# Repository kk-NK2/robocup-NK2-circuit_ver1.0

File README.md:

交流会用に作った初めての回路です。
らずピコとアルディーノのuart通信でレベル変換をしていなかったため、燃えます。

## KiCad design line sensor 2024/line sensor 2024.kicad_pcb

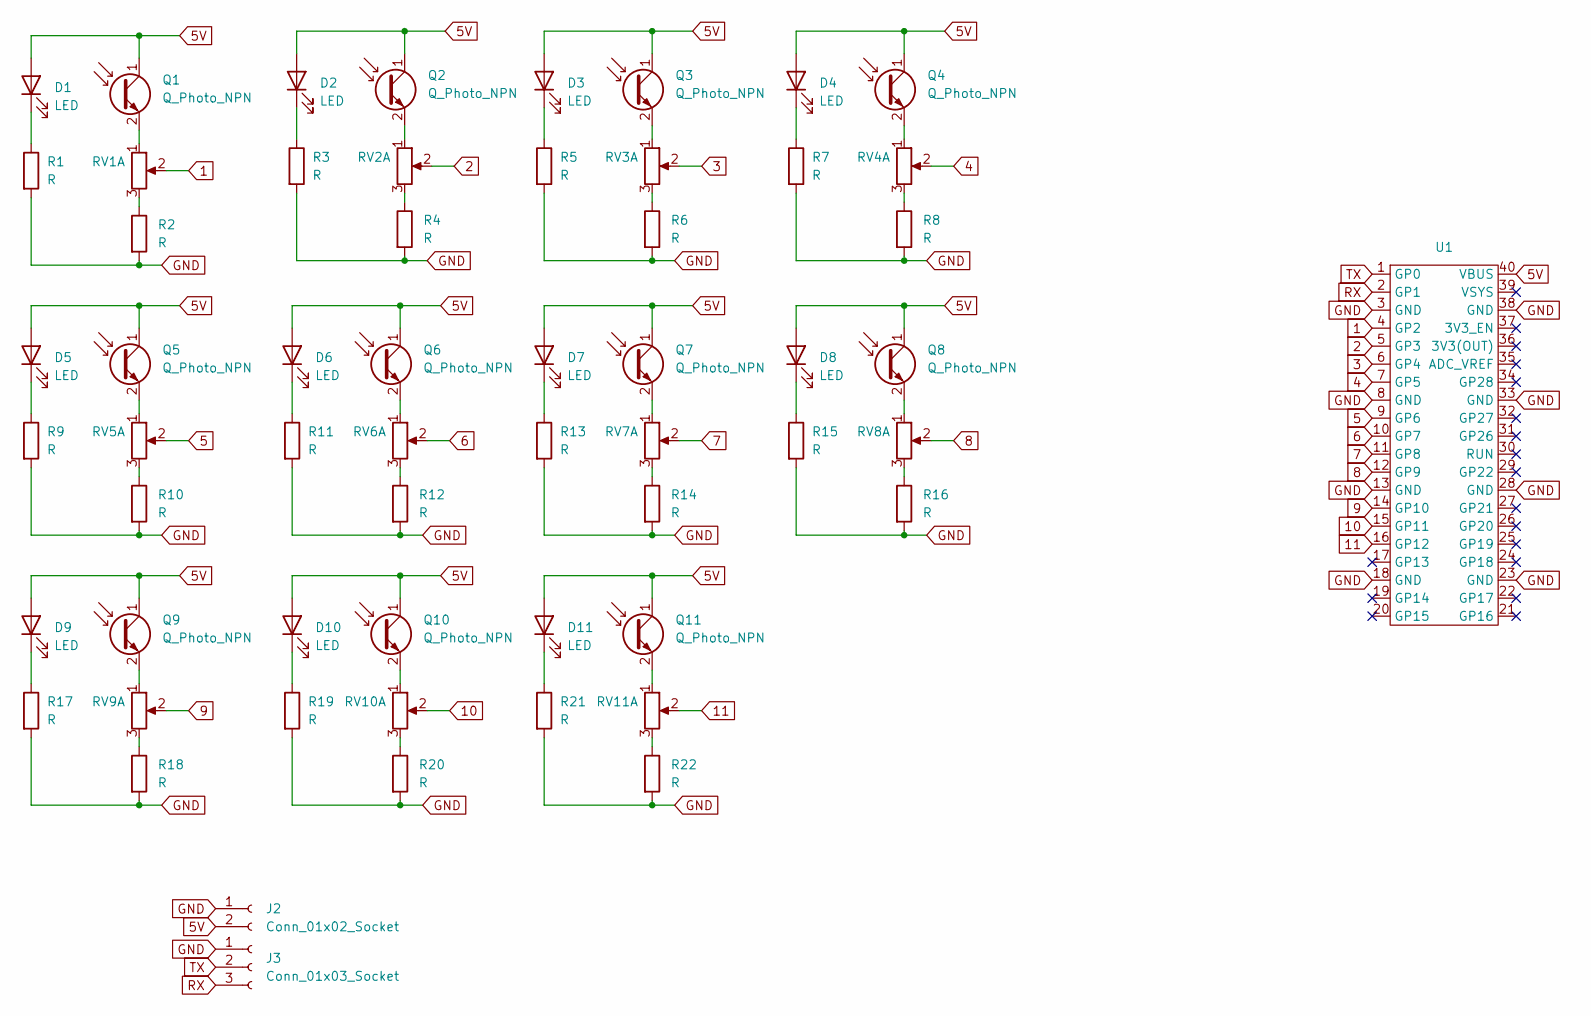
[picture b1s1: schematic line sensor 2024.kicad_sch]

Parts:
D1, D2, D3, D4, D5, D6, D7, D8, D9, D10, D11: LED; LED_D3.0mm_Clear
J2: Conn_01x02_Socket; JST_XH_B2B-XH-AM_1x02_P2.50mm_Vertical
J3: Conn_01x03_Socket; JST_XH_B3B-XH-AM_1x03_P2.50mm_Vertical
Q1, Q2, Q3, Q4, Q5, Q6, Q7, Q8, Q9, Q10, Q11: Q_Photo_NPN; LED_D4.0mm
R1, R2, R3, R4, R5, R6, R7, R8, R9, R10, R11, R12, R13, R14, R15, R16, R17, R18, R19, R20, R21, R22: R; R_Axial_DIN0207_L6.3mm_D2.5mm_P10.16mm_Horizontal
RV1, RV2, RV3, RV4, RV5, RV6, RV7, RV8, RV9, RV10, RV11: R_Potentiometer_Dual_Separate; Potentiometer_Vishay_T73YP_Vertical
U1: RP pico

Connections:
1: RV1.2, U1.4 (GP2)
2: RV2.2, U1.5 (GP3)
3: RV3.2, U1.6 (GP4)
4: RV4.2, U1.7 (GP5)
5: RV5.2, U1.9 (GP6)
5V: D1.2 (A), D2.2 (A), D3.2 (A), D4.2 (A), D5.2 (A), D6.2 (A), D7.2 (A), D8.2 (A), D9.2 (A), D10.2 (A), D11.2 (A), J2.2, Q1.1 (C), Q2.1 (C), Q3.1 (C), Q4.1 (C), Q5.1 (C), Q6.1 (C), Q7.1 (C), Q8.1 (C), Q9.1 (C), Q10.1 (C), Q11.1 (C), U1.40 (VBUS)
6: RV6.2, U1.10 (GP7)
7: RV7.2, U1.11 (GP8)
8: RV8.2, U1.12 (GP9)
9: RV9.2, U1.14 (GP10)
10: RV10.2, U1.15 (GP11)
11: RV11.2, U1.16 (GP12)
GND: J2.1, J3.1, R1.2, R2.2, R3.2, R4.2, R5.2, R6.2, R7.2, R8.2, R9.2, R10.2, R11.2, R12.2, R13.2, R14.2, R15.2, R16.2, R17.2, R18.2, R19.2, R20.2, R21.2, R22.2, U1.3 (GND), U1.8 (GND), U1.13 (GND), U1.18 (GND), U1.23 (GND), U1.28 (GND), U1.33 (GND), U1.38 (GND)
unnamed: D1.1 (K), R1.1
unnamed: D2.1 (K), R3.1
unnamed: D3.1 (K), R5.1
unnamed: D4.1 (K), R7.1
unnamed: D5.1 (K), R9.1
unnamed: D6.1 (K), R11.1
unnamed: D7.1 (K), R13.1
unnamed: D8.1 (K), R15.1
unnamed: D9.1 (K), R17.1
unnamed: D10.1 (K), R19.1
unnamed: D11.1 (K), R21.1
unnamed: Q1.2 (E), RV1.1
unnamed: Q2.2 (E), RV2.1
unnamed: Q3.2 (E), RV3.1
unnamed: Q4.2 (E), RV4.1
unnamed: Q5.2 (E), RV5.1
unnamed: Q6.2 (E), RV6.1
unnamed: Q7.2 (E), RV7.1
unnamed: Q8.2 (E), RV8.1
unnamed: Q9.2 (E), RV9.1
unnamed: Q10.2 (E), RV10.1
unnamed: Q11.2 (E), RV11.1
unnamed: R2.1, RV1.3
unnamed: R4.1, RV2.3
unnamed: R6.1, RV3.3
unnamed: R8.1, RV4.3
unnamed: R10.1, RV5.3
unnamed: R12.1, RV6.3
unnamed: R14.1, RV7.3
unnamed: R16.1, RV8.3
unnamed: R18.1, RV9.3
unnamed: R20.1, RV10.3
unnamed: R22.1, RV11.3
RX: J3.3, U1.2 (GP1)
TX: J3.2, U1.1 (GP0)

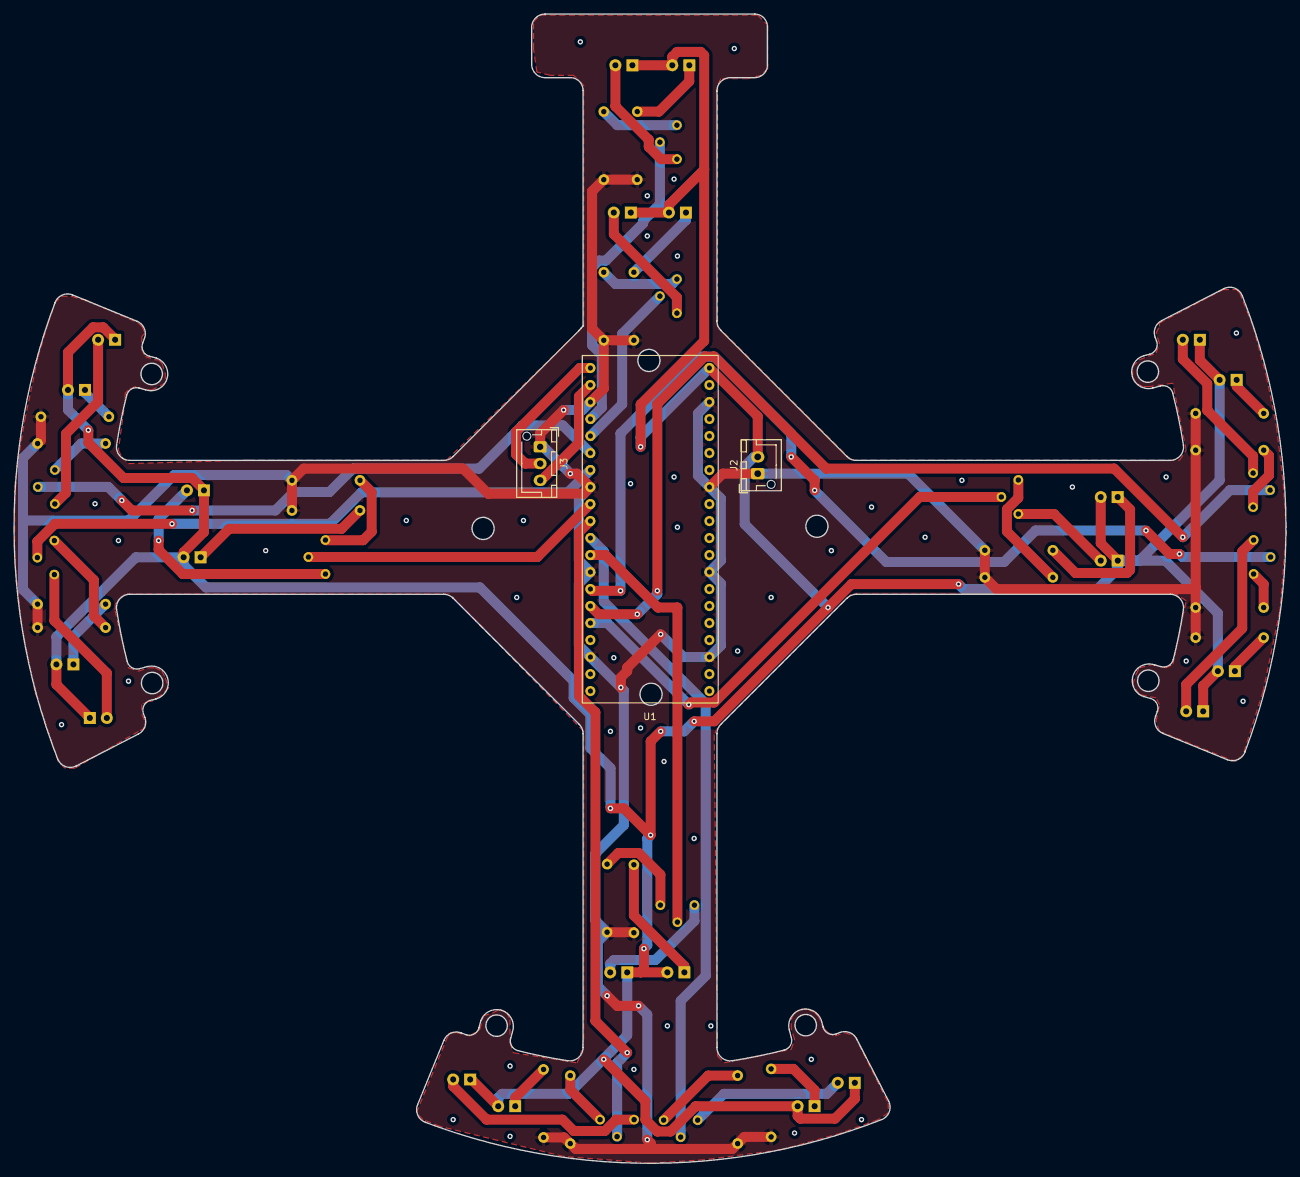
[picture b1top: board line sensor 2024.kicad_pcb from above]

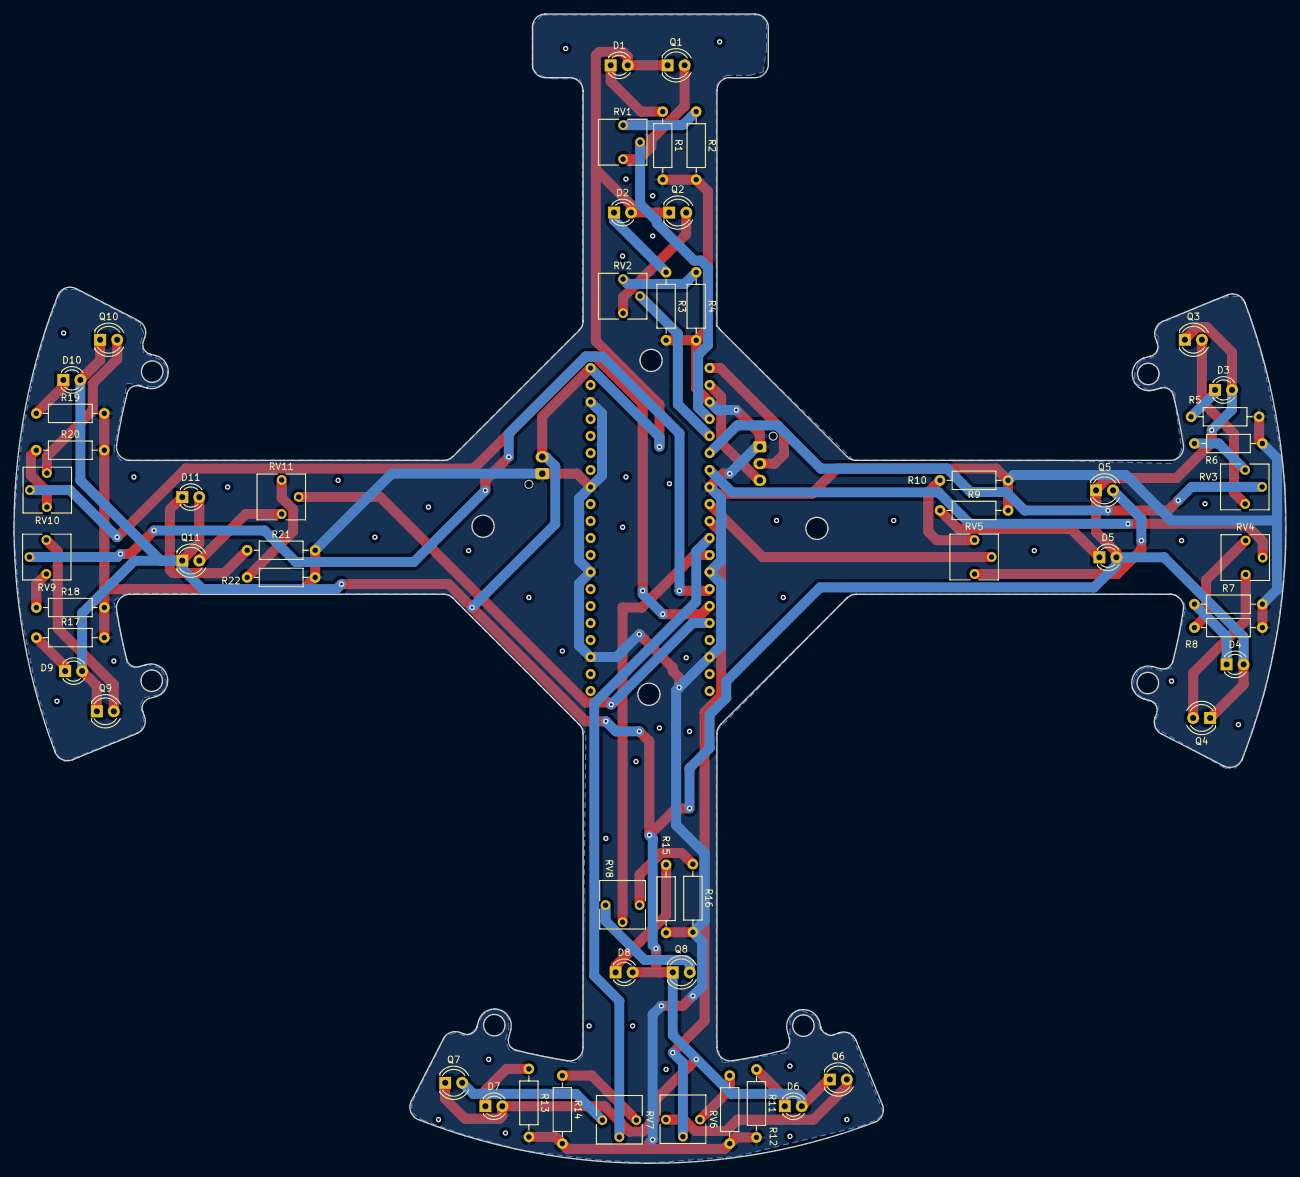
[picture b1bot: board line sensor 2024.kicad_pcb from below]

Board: 2 copper layers, 190.0 x 171.7 mm, 58 parts (55 on the bottom side), 48 nets.

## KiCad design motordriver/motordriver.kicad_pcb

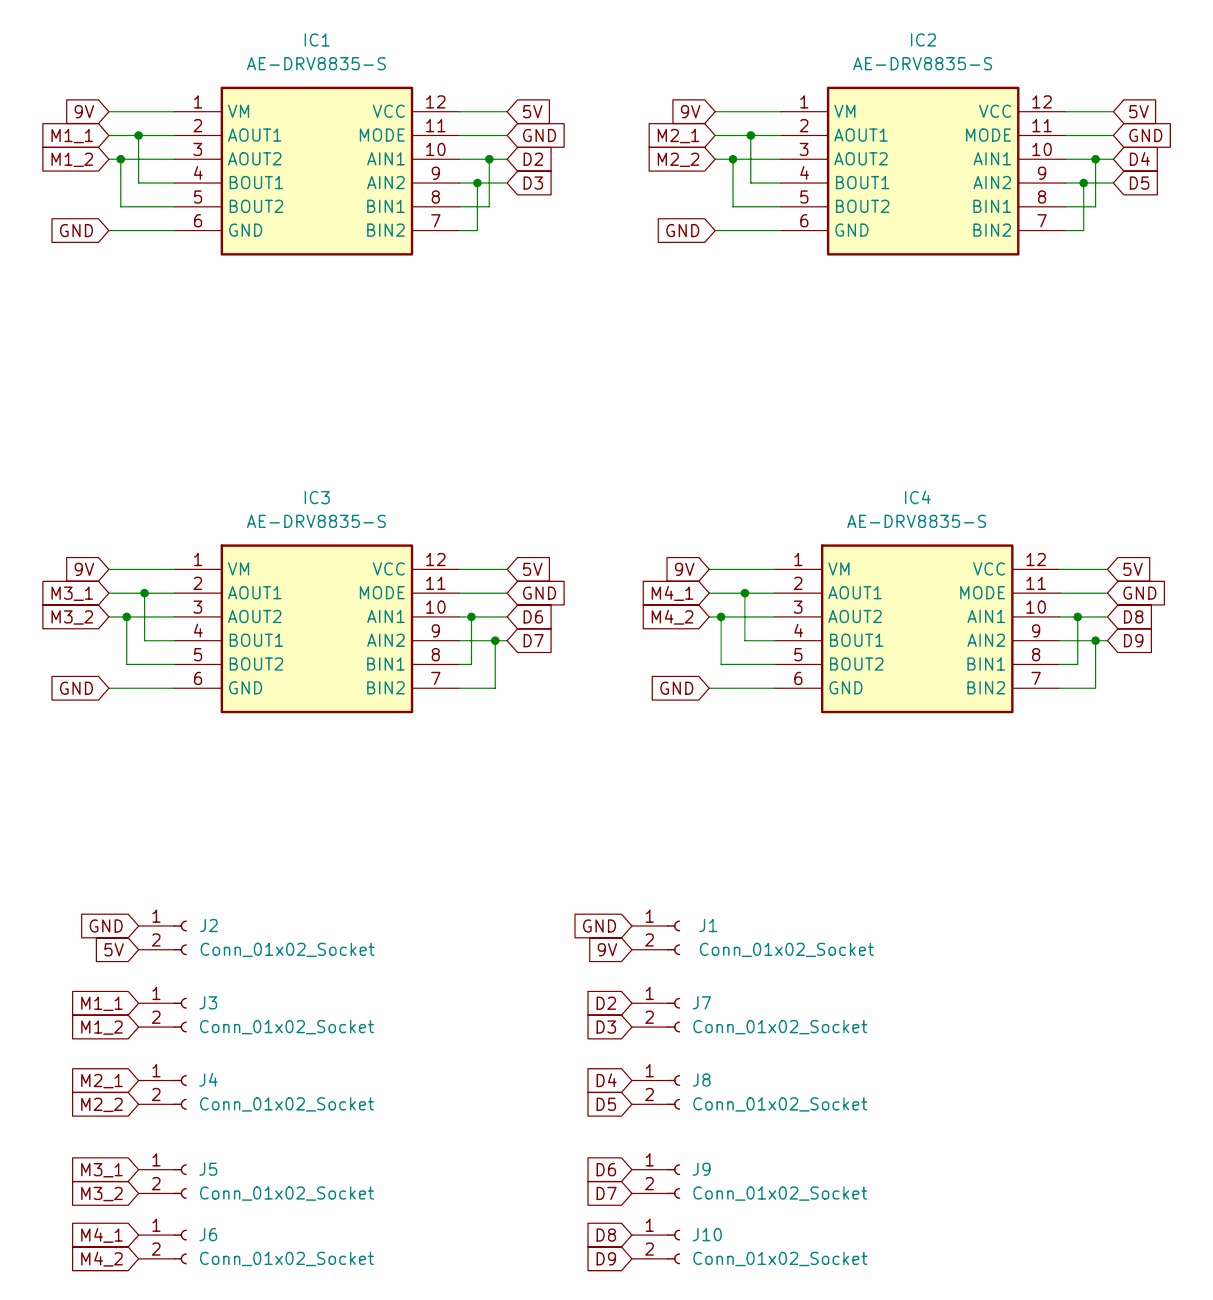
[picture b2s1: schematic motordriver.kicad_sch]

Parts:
IC1, IC2, IC3, IC4: AE-DRV8835-S; AEDRV8835S; Manufacturer_Part_Number AE-DRV8835-S
J1, J2, J3, J4, J5, J6, J7, J8, J9, J10: Conn_01x02_Socket; JST_XH_B2B-XH-AM_1x02_P2.50mm_Vertical

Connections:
5V: IC1.12 (VCC), IC2.12 (VCC), IC3.12 (VCC), IC4.12 (VCC), J2.2
9V: IC1.1 (VM), IC2.1 (VM), IC3.1 (VM), IC4.1 (VM), J1.2
D2: IC1.8 (BIN1), IC1.10 (AIN1), J7.1
D3: IC1.7 (BIN2), IC1.9 (AIN2), J7.2
D4: IC2.8 (BIN1), IC2.10 (AIN1), J8.1
D5: IC2.7 (BIN2), IC2.9 (AIN2), J8.2
D6: IC3.8 (BIN1), IC3.10 (AIN1), J9.1
D7: IC3.7 (BIN2), IC3.9 (AIN2), J9.2
D8: IC4.8 (BIN1), IC4.10 (AIN1), J10.1
D9: IC4.7 (BIN2), IC4.9 (AIN2), J10.2
GND: IC1.6 (GND), IC1.11 (MODE), IC2.6 (GND), IC2.11 (MODE), IC3.6 (GND), IC3.11 (MODE), IC4.6 (GND), IC4.11 (MODE), J1.1, J2.1
M1_1: IC1.2 (AOUT1), IC1.4 (BOUT1), J3.1
M1_2: IC1.3 (AOUT2), IC1.5 (BOUT2), J3.2
M2_1: IC2.2 (AOUT1), IC2.4 (BOUT1), J4.1
M2_2: IC2.3 (AOUT2), IC2.5 (BOUT2), J4.2
M3_1: IC3.2 (AOUT1), IC3.4 (BOUT1), J5.1
M3_2: IC3.3 (AOUT2), IC3.5 (BOUT2), J5.2
M4_1: IC4.2 (AOUT1), IC4.4 (BOUT1), J6.1
M4_2: IC4.3 (AOUT2), IC4.5 (BOUT2), J6.2

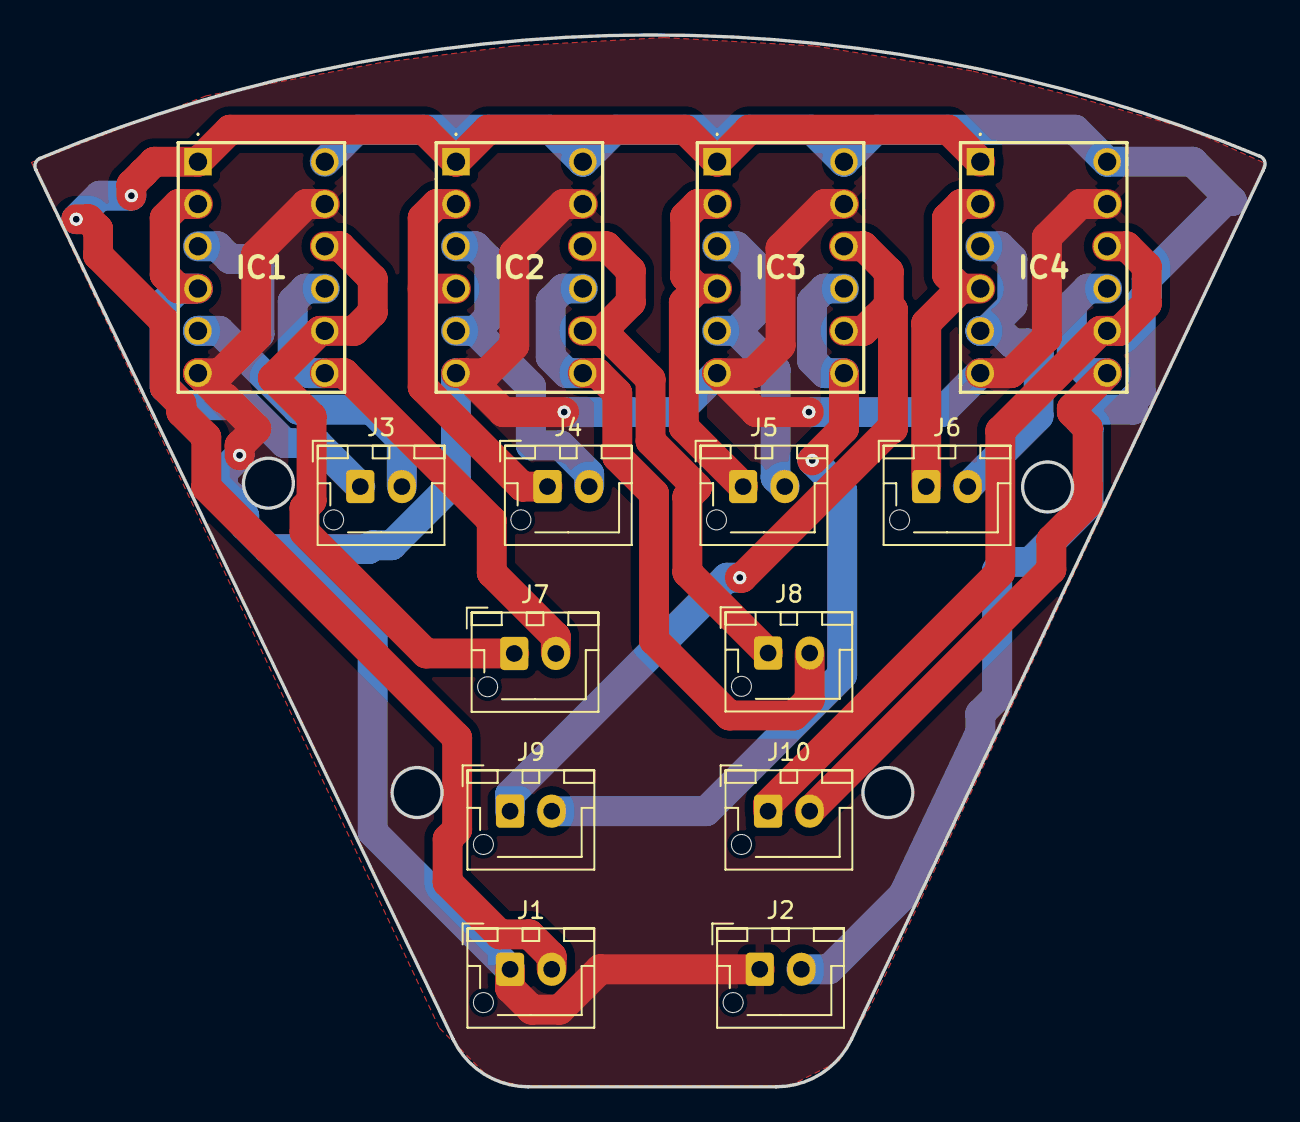
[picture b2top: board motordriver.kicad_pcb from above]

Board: 2 copper layers, 73.9 x 63.2 mm, 14 parts (0 on the bottom side), 19 nets.

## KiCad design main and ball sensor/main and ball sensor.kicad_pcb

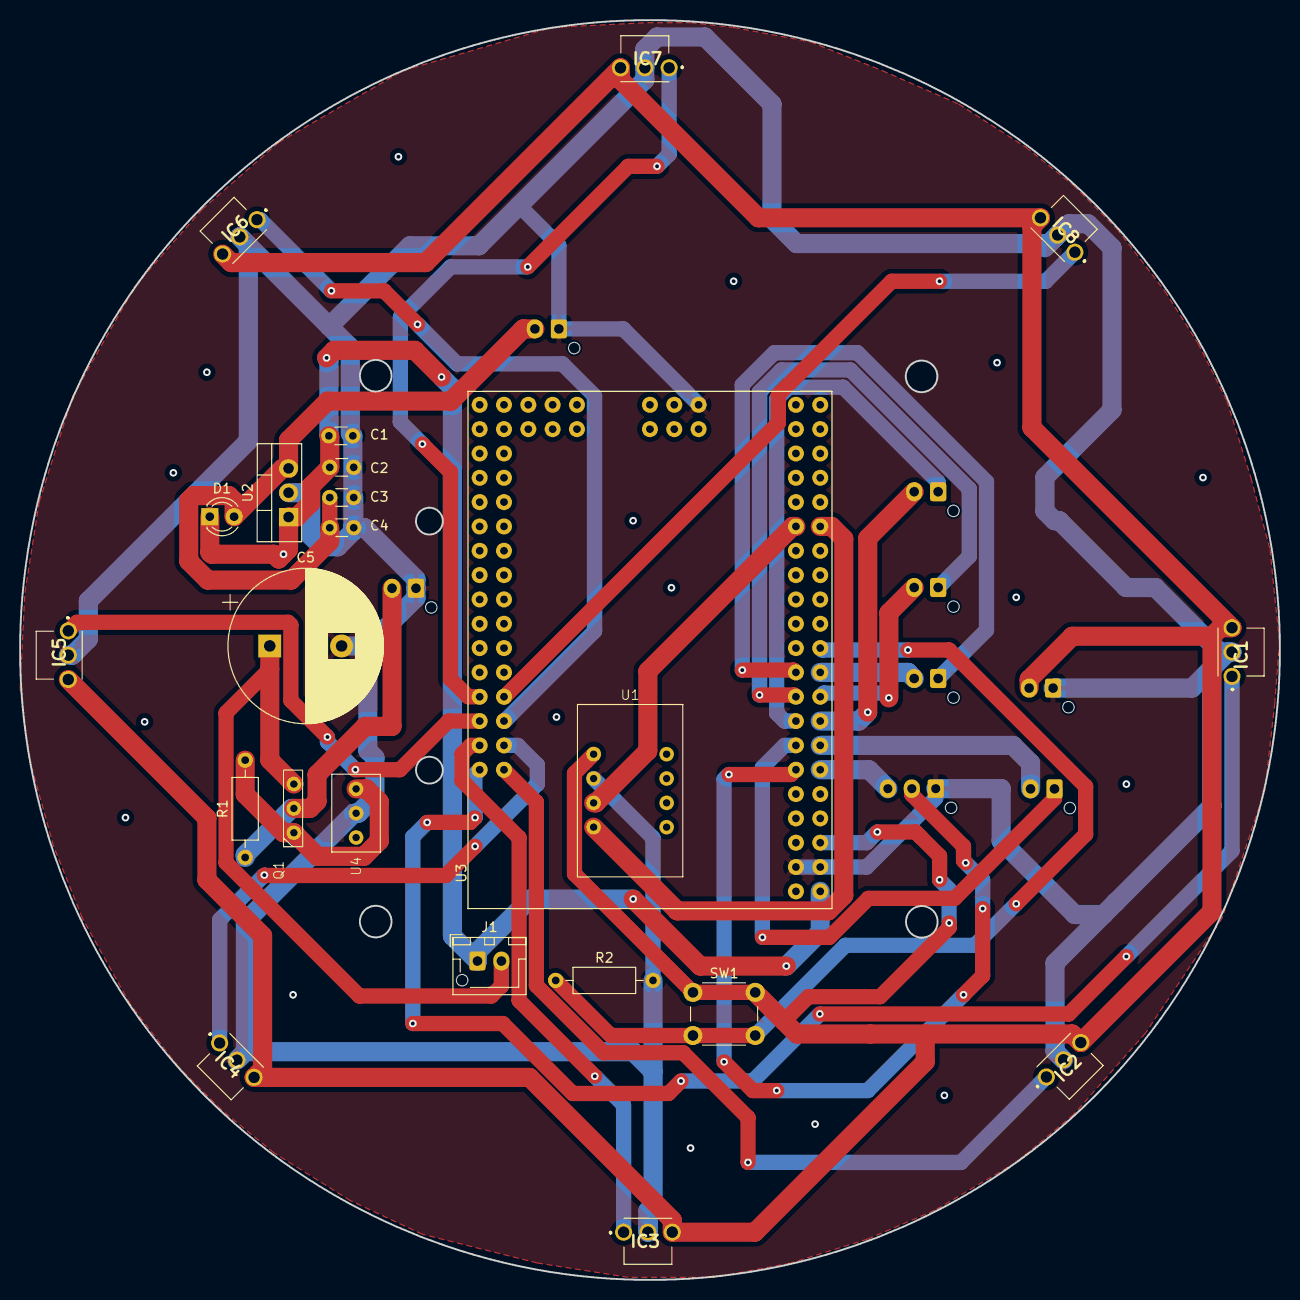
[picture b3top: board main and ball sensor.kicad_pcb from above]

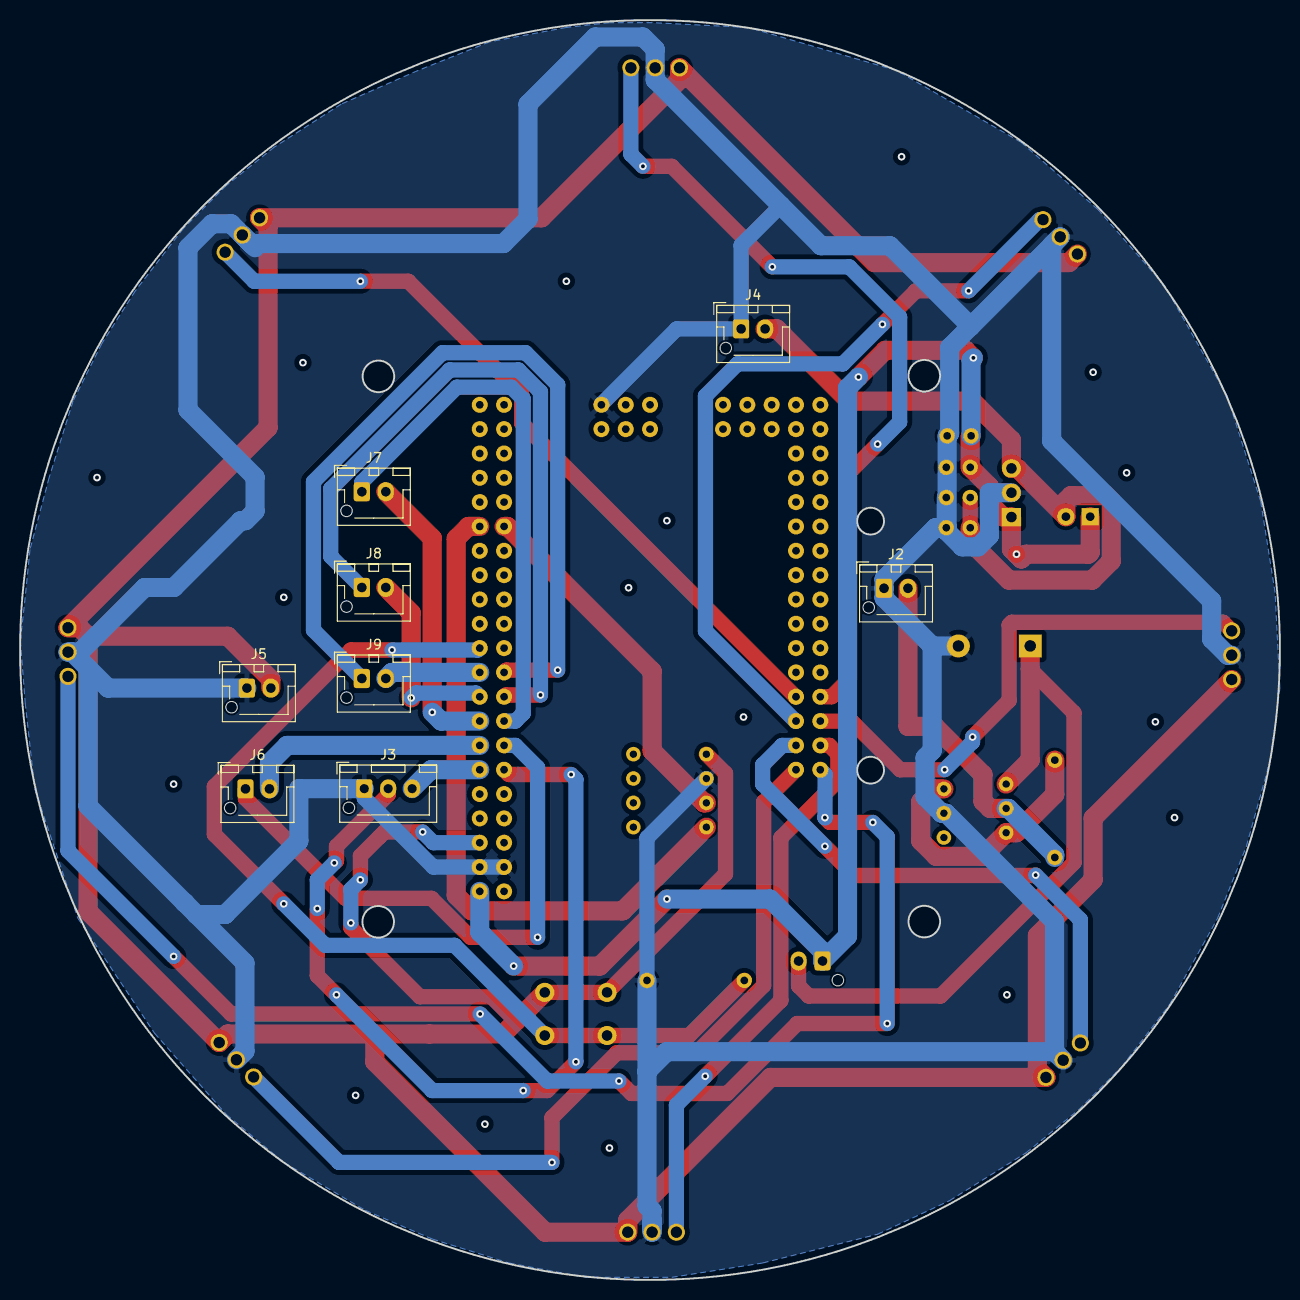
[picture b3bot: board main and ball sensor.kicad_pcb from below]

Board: 2 copper layers, 131.5 x 131.5 mm, 31 parts (8 on the bottom side), 28 nets.

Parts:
C1, C4: 0.1u; C_Disc_D3.0mm_W1.6mm_P2.50mm
C2: 10u; C_Disc_D3.0mm_W1.6mm_P2.50mm
C3: 47u; C_Disc_D3.0mm_W1.6mm_P2.50mm
C5: C_Polarized; CP_Radial_D16.0mm_P7.50mm
D1: D; LED_D3.0mm_Clear
IC1, IC2, IC3, IC4, IC5, IC6, IC7, IC8: TSSP58038
J1, J2, J4, J5, J6, J7, J8, J9: Conn_01x02_Socket; JST_XH_B2B-XH-AM_1x02_P2.50mm_Vertical
J3: Conn_01x03_Socket; JST_XH_B3B-XH-AM_1x03_P2.50mm_Vertical
Q1: PMOS; mosfet.pch
R1, R2: R; R_Axial_DIN0207_L6.3mm_D2.5mm_P10.16mm_Horizontal
SW1: SW_Push; SW_PUSH_6mm_H7.3mm
U1: BNO055+
U2: L7805; TO-220-3_Vertical
U3: MEGA_PRO_EMBED_CH340G___ATMEGA2560; MODULE_MEGA_PRO_EMBED_CH340G___ATMEGA2560
U4: tgul

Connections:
0: IC1.1 (OUT), U3.A0
1: IC2.1 (OUT), U3.A1
2: IC3.1 (OUT), U3.A2
3: IC4.1 (OUT), U3.A3
4: IC5.1 (OUT), U3.A4
5: IC6.1 (OUT), U3.A5
5V: IC1.3 (VS), IC2.3 (VS), IC3.3 (VS), IC4.3 (VS), IC5.3 (VS), IC6.3 (VS), IC7.3 (VS), IC8.3 (VS), J5.2, SW1.1, U1.1 (Vin), U3.5V_1 (5V)
5V_1: C3.1, C4.1, D1.2 (A), J4.2, U2.3 (OUT)
6: IC7.1 (OUT), U3.A6
7: IC8.1 (OUT), U3.A7
9V: C1.1, C2.1, D1.1 (K), J1.1, U2.1 (IN), U3.VIN_1 (VIN)
D2: J6.1, U3.D2
D3: J6.2, U3.D3
D4: J7.1, U3.D4
D5: J7.2, U3.D5
D6: J8.1, U3.D6
D7: J8.2, U3.D7
D8: J9.1, U3.D8
D9: J9.2, U3.D9
D11: R2.1, SW1.2, U3.D11
GND: C1.2, C2.2, C3.2, C4.2, C5.2, IC1.2 (GND), IC2.2 (GND), IC3.2 (GND), IC4.2 (GND), IC5.2 (GND), IC6.2 (GND), IC7.2 (GND), IC8.2 (GND), J2.1, J3.1, J4.1, J5.1, R2.2, U1.2 (GND), U2.2 (GND), U3.GND_1 (GND), U3.GND_2 (GND__1), U3.GND_3 (GND__2), U4.2 (N)
unnamed: Q1.2 (G), R1.2, U4.3 (ON)
RX: J3.2, U3.RX
SCL: U1.4 (SCL), U3.D21
SDA: U1.3 (SDA), U3.D20
TX: J3.3, U3.TX
Vin: J2.2, Q1.3 (S), R1.1
Vin_1: C5.1, J1.2, Q1.1 (D)

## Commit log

2024-08-27 NK2_circuit_ver_1
    circuit
